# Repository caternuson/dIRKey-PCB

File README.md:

# dIRKey-PCB
Developmental IR USB HID Board

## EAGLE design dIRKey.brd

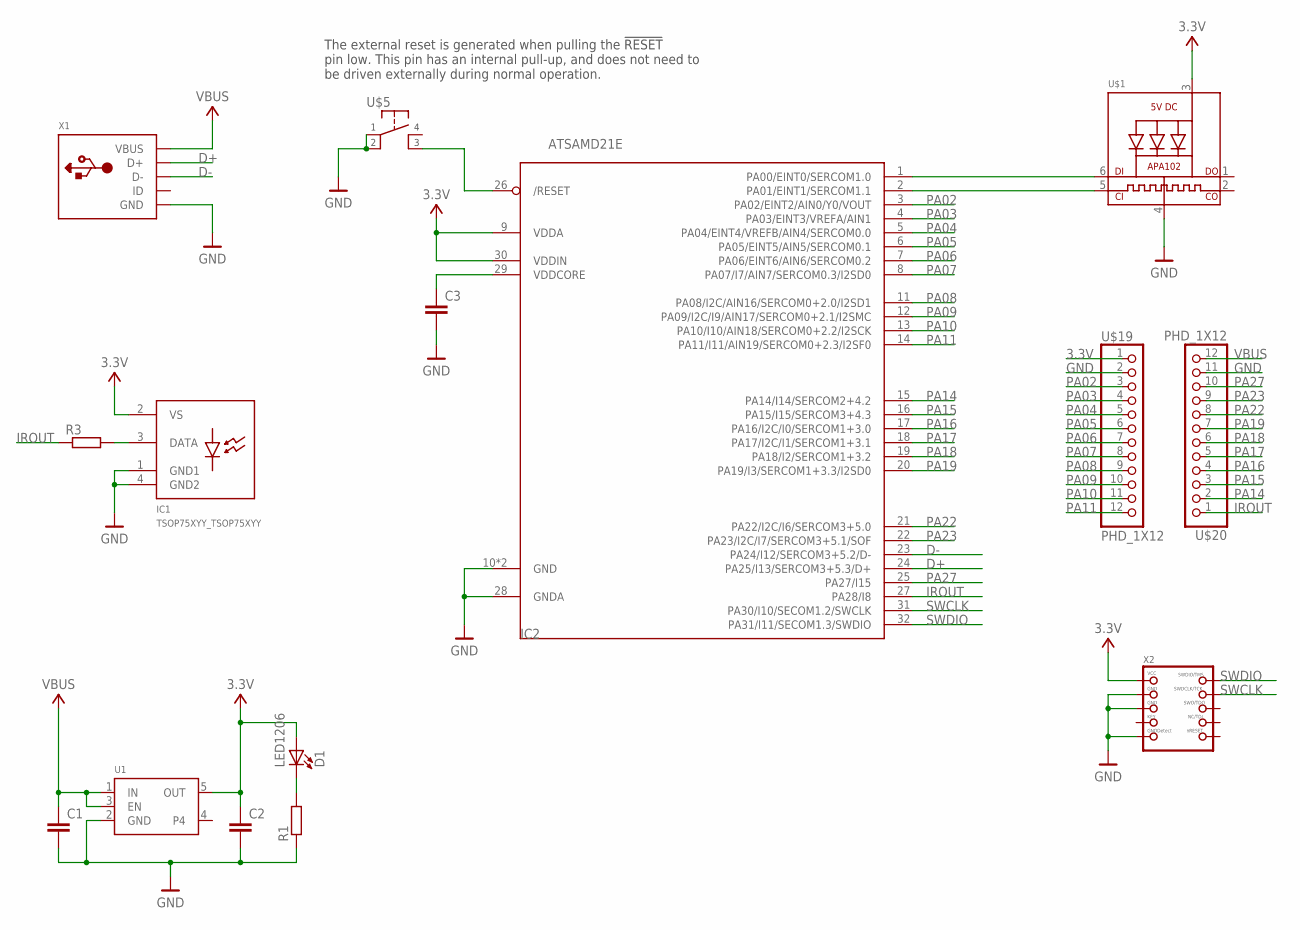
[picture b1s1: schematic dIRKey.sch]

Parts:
C1, C2, C3: C-EUC1206; C1206
D1: LED1206
IC1: TSOP75XYY_TSOP75XYY
IC2: ATSAMD21E; QFN32_5MM
R1, R3: R-EU_R1206; R1206
U1: AP2112K; SOT23-5
U$1: DOTSTAR_APA1022020; APA102_2020
U$5: PTS647
U$19, U$20: PHD_1X12
X1: USB_MICRO_BMICRO_20329; USB_MICRO_B
X2: SWD_2X5; SWD_MINI

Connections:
3.3V: C2.1, D1.2 (A), IC1.2 (VS), IC2.9 (VDDA), IC2.30 (VDDIN), U1.5 (OUT), U$1.3 (VDD), U$19.1, X2.1 (VCC)
D+: IC2.24 (PA25/I13/SERCOM3+5.3/D+), X1.D+
D-: IC2.23 (PA24/I12/SERCOM3+5.2/D-), X1.D-
GND: C1.2, C2.2, C3.2, IC1.1 (GND1), IC1.4 (GND2), IC2.10 (GND), IC2.28 (GNDA), IC2.33 (GND), R1.1, U1.2 (GND), U$1.4 (GND), U$5.1, U$5.2, U$19.2, U$20.11, X1.BASE@1 (GND), X1.BASE@2 (GND), X1.GND, X1.SPRT@1 (GND), X1.SPRT@2 (GND), X1.SPRT@3 (GND), X1.SPRT@4 (GND), X2.3 (GND), X2.5 (GND), X2.9 (GNDDETECT)
IROUT: IC2.27 (PA28/I8), R3.1, U$20.1
unnamed: IC2.1 (PA00/EINT0/SERCOM1.0), U$1.6 (DI)
unnamed: IC2.2 (PA01/EINT1/SERCOM1.1), U$1.5 (CKI)
unnamed: D1.1 (C), R1.2
unnamed: IC1.3 (DATA), R3.2
unnamed: C3.1, IC2.29 (VDDCORE)
unnamed: IC2.26 (/RESET), U$5.3
PA02: IC2.3 (PA02/EINT2/AIN0/Y0/VOUT), U$19.3
PA03: IC2.4 (PA03/EINT3/VREFA/AIN1), U$19.4
PA04: IC2.5 (PA04/EINT4/VREFB/AIN4/SERCOM0.0), U$19.5
PA05: IC2.6 (PA05/EINT5/AIN5/SERCOM0.1), U$19.6
PA06: IC2.7 (PA06/EINT6/AIN6/SERCOM0.2), U$19.7
PA07: IC2.8 (PA07/I7/AIN7/SERCOM0.3/I2SD0), U$19.8
PA08: IC2.11 (PA08/I2C/AIN16/SERCOM0+2.0/I2SD1), U$19.9
PA09: IC2.12 (PA09/I2C/I9/AIN17/SERCOM0+2.1/I2SMC), U$19.10
PA10: IC2.13 (PA10/I10/AIN18/SERCOM0+2.2/I2SCK), U$19.11
PA11: IC2.14 (PA11/I11/AIN19/SERCOM0+2.3/I2SF0), U$19.12
PA14: IC2.15 (PA14/I14/SERCOM2+4.2), U$20.2
PA15: IC2.16 (PA15/I15/SERCOM3+4.3), U$20.3
PA16: IC2.17 (PA16/I2C/I0/SERCOM1+3.0), U$20.4
PA17: IC2.18 (PA17/I2C/I1/SERCOM1+3.1), U$20.5
PA18: IC2.19 (PA18/I2/SERCOM1+3.2), U$20.6
PA19: IC2.20 (PA19/I3/SERCOM1+3.3/I2SD0), U$20.7
PA22: IC2.21 (PA22/I2C/I6/SERCOM3+5.0), U$20.8
PA23: IC2.22 (PA23/I2C/I7/SERCOM3+5.1/SOF), U$20.9
PA27: IC2.25 (PA27/I15), U$20.10
SWCLK: IC2.31 (PA30/I10/SECOM1.2/SWCLK), X2.4 (SWDCLK)
SWDIO: IC2.32 (PA31/I11/SECOM1.3/SWDIO), X2.2 (SWDIO)
VBUS: C1.1, U1.1 (IN), U1.3 (EN), U$20.12, X1.VBUS

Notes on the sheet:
The external reset is generated when pulling the !RESET pin low. This pin has an internal pull-up, and does not need to be driven externally during normal operation.

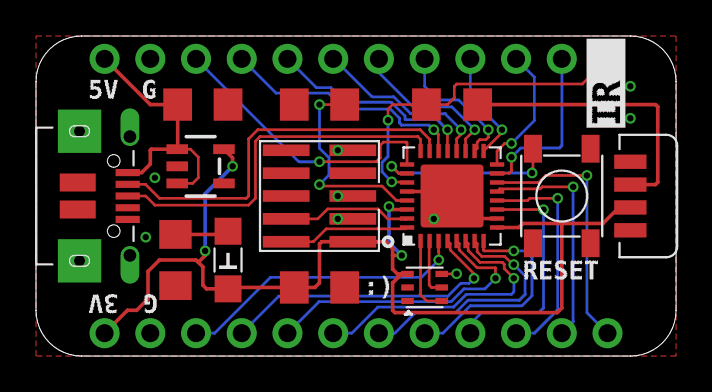
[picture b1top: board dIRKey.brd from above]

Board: 2 copper layers, 35.6 x 17.8 mm, 15 parts (0 on the bottom side), 33 nets.

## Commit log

2021-02-07 add files
